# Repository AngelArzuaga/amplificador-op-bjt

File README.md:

# Amplificador Operacional con BJTs

Diseño de un amplificador operacional discreto construido con transistores BJT, incluyendo esquemático, simulación en LTspice y layout en KiCad.
### Integrantes:
Ángel Arzuaga, María Camila Castilla, Cristian Sepúlveda y Esteban Toro

## Descripción

Este proyecto consiste en construir, desde cero, un amplificador operacional usando transistores bipolares individuales, en lugar de partir de un circuito integrado ya armado. La idea es entender cómo funciona por dentro un componente que normalmente se usa como una "caja negra", diseñando cada etapa del circuito; entrada, amplificación y salida.

Una vez terminado el diseño, se puso a prueba el circuito en dos configuraciones clásicas para verificar que funcionara correctamente. La primera fue como amplificador no inversor con ganancia 2, es decir, la señal de salida sale duplicada respecto a la de entrada, manteniendo la misma polaridad. La segunda fue como buffer (o seguidor de voltaje), una configuración que no amplifica la señal pero es muy útil para aislar etapas de un circuito sin alterar el voltaje que pasa por ellas.

## Simulación en LTspice

*Esquemático simulado en LTspice, base de los resultados de ganancia y ancho de banda.*

*Esquemático simulado en LTspice, en configuración no inversora de ganancia 2.*

*Esquemático simulado en LTspice, en configuración de buffer.*

## Esquemático en KiCad

*Esquemático completo del amplificador diseñado en KiCad.*

## PCB

*Distribución de componentes y pistas del PCB.*

*Render 3D del PCB terminado.*

*PCB terminado con componentes soldados.*

## Componentes utilizados

| Componente | Valor / Modelo | Datasheet |
|---|---|---|
| NPN | 2N3904 | [datasheet](datasheets/2N3904.pdf) |
| PNP | 2N3906 | [datasheet](datasheets/2N3906.pdf) |
| $R_{ref}$ | 10 kΩ | — |
| $C_1$ | 100 nF | — |

El amplificador se diseño para que tanto $R_{ref}$ como $C_1$ puedan ser intercambiables a gusto del diseñador o usuario final.

## Estructura del repositorio

```
amplificador-op-bjt/
├── kicad/          # Esquemático y PCB (KiCad)
├── ltspice/         # Simulaciones y resultados (LTspice)
├── datasheets/       # Hojas de datos de los componentes usados
├── docs/
│   └── images/         # Capturas de esquemático, gráficas, fotos
├── gerbers/           # Archivos de fabricación del PCB
└── LICENSE
```

## Cómo abrir los archivos

**KiCad** (versión 9.0 o superior):
1. Abre KiCad
2. File → Open Project → selecciona `kicad/amp-op-bjt.kicad_pro`

**LTspice**:
1. Abre LTspice
2. File → Open → selecciona el archivo `.asc` dentro de `ltspice/`
3. Ejecuta la simulación con Simulate → Run

## Licencia

Este proyecto está licenciado bajo **CERN-OHL-P v2**. Ver [LICENSE](LICENSE) para el texto completo.

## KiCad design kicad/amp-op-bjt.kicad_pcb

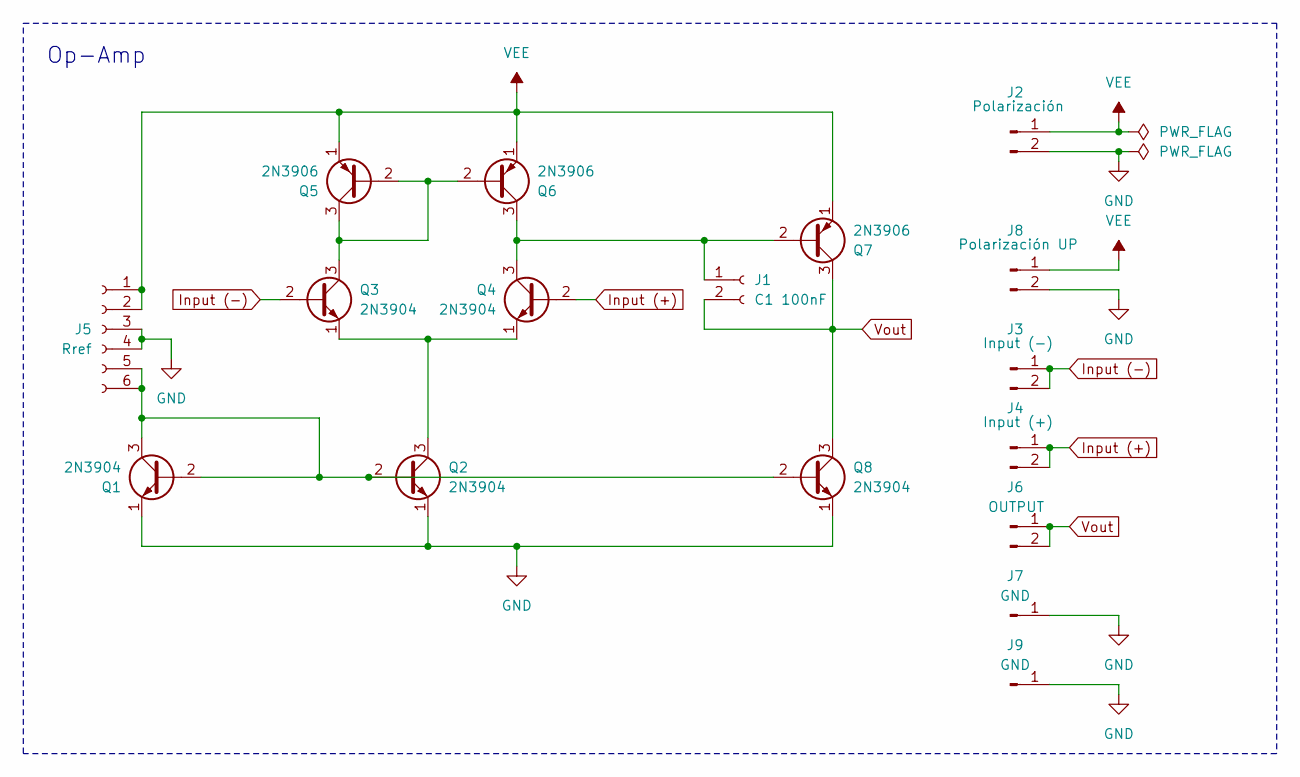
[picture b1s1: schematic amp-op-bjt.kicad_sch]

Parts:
J1: C1 100nF; PinSocket_1x02_P2.54mm_Vertical
J2: Polarización; PinHeader_1x02_P2.54mm_Vertical
J3: Input (-); PinHeader_1x02_P2.54mm_Vertical
J4: Input (+); PinHeader_1x02_P2.54mm_Vertical
J5: Rref; PinSocket_1x06_P2.54mm_Vertical
J6: OUTPUT; PinHeader_1x02_P2.54mm_Vertical
J7, J9: GND; PinHeader_1x01_P2.54mm_Vertical
J8: Polarización UP; PinHeader_1x02_P2.54mm_Vertical
Q1, Q2, Q3, Q4, Q8: 2N3904; TO-92_Inline_Wide
Q5, Q6, Q7: 2N3906; TO-92_Inline_Wide

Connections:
GND: J2.2, J5.3, J5.4, J7.1, J8.2, J9.1, Q1.1 (E), Q2.1 (E), Q8.1 (E)
Input (+): J4.1, J4.2, Q4.2 (B)
Input (-): J3.1, J3.2, Q3.2 (B)
unnamed: J1.1, Q4.3 (C), Q6.3 (C), Q7.2 (B)
unnamed: J5.5, J5.6, Q1.2 (B), Q1.3 (C), Q2.2 (B), Q8.2 (B)
unnamed: Q2.3 (C), Q3.1 (E), Q4.1 (E)
unnamed: Q3.3 (C), Q5.2 (B), Q5.3 (C), Q6.2 (B)
VEE: J2.1, J5.1, J5.2, J8.1, Q5.1 (E), Q6.1 (E), Q7.1 (E)
Vout: J1.2, J6.1, J6.2, Q7.3 (C), Q8.3 (C)

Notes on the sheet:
Op-Amp

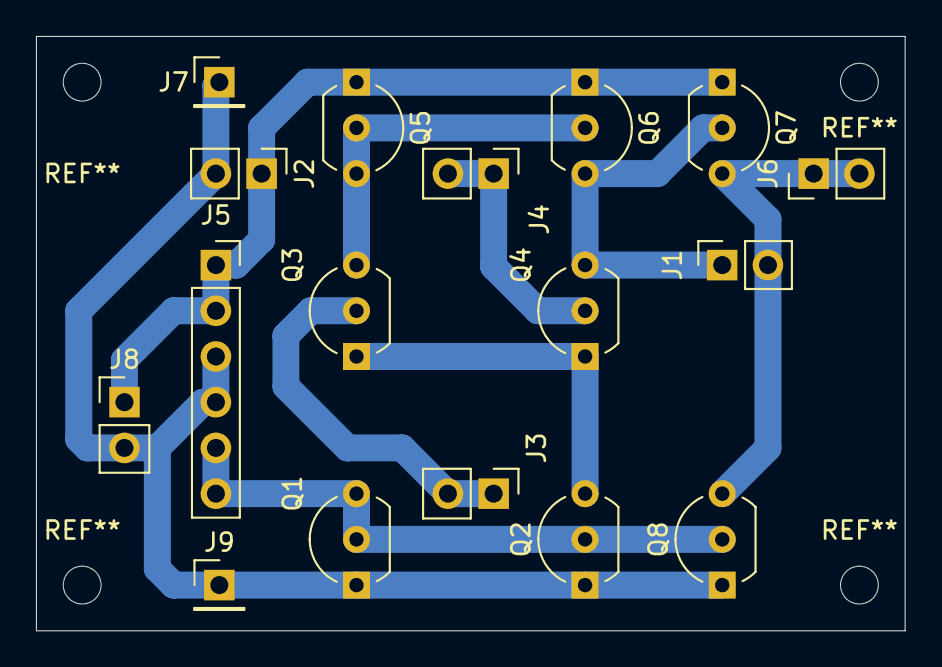
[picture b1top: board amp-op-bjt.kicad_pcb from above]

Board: 2 copper layers, 48.3 x 33.0 mm, 17 parts (0 on the bottom side), 9 nets.
